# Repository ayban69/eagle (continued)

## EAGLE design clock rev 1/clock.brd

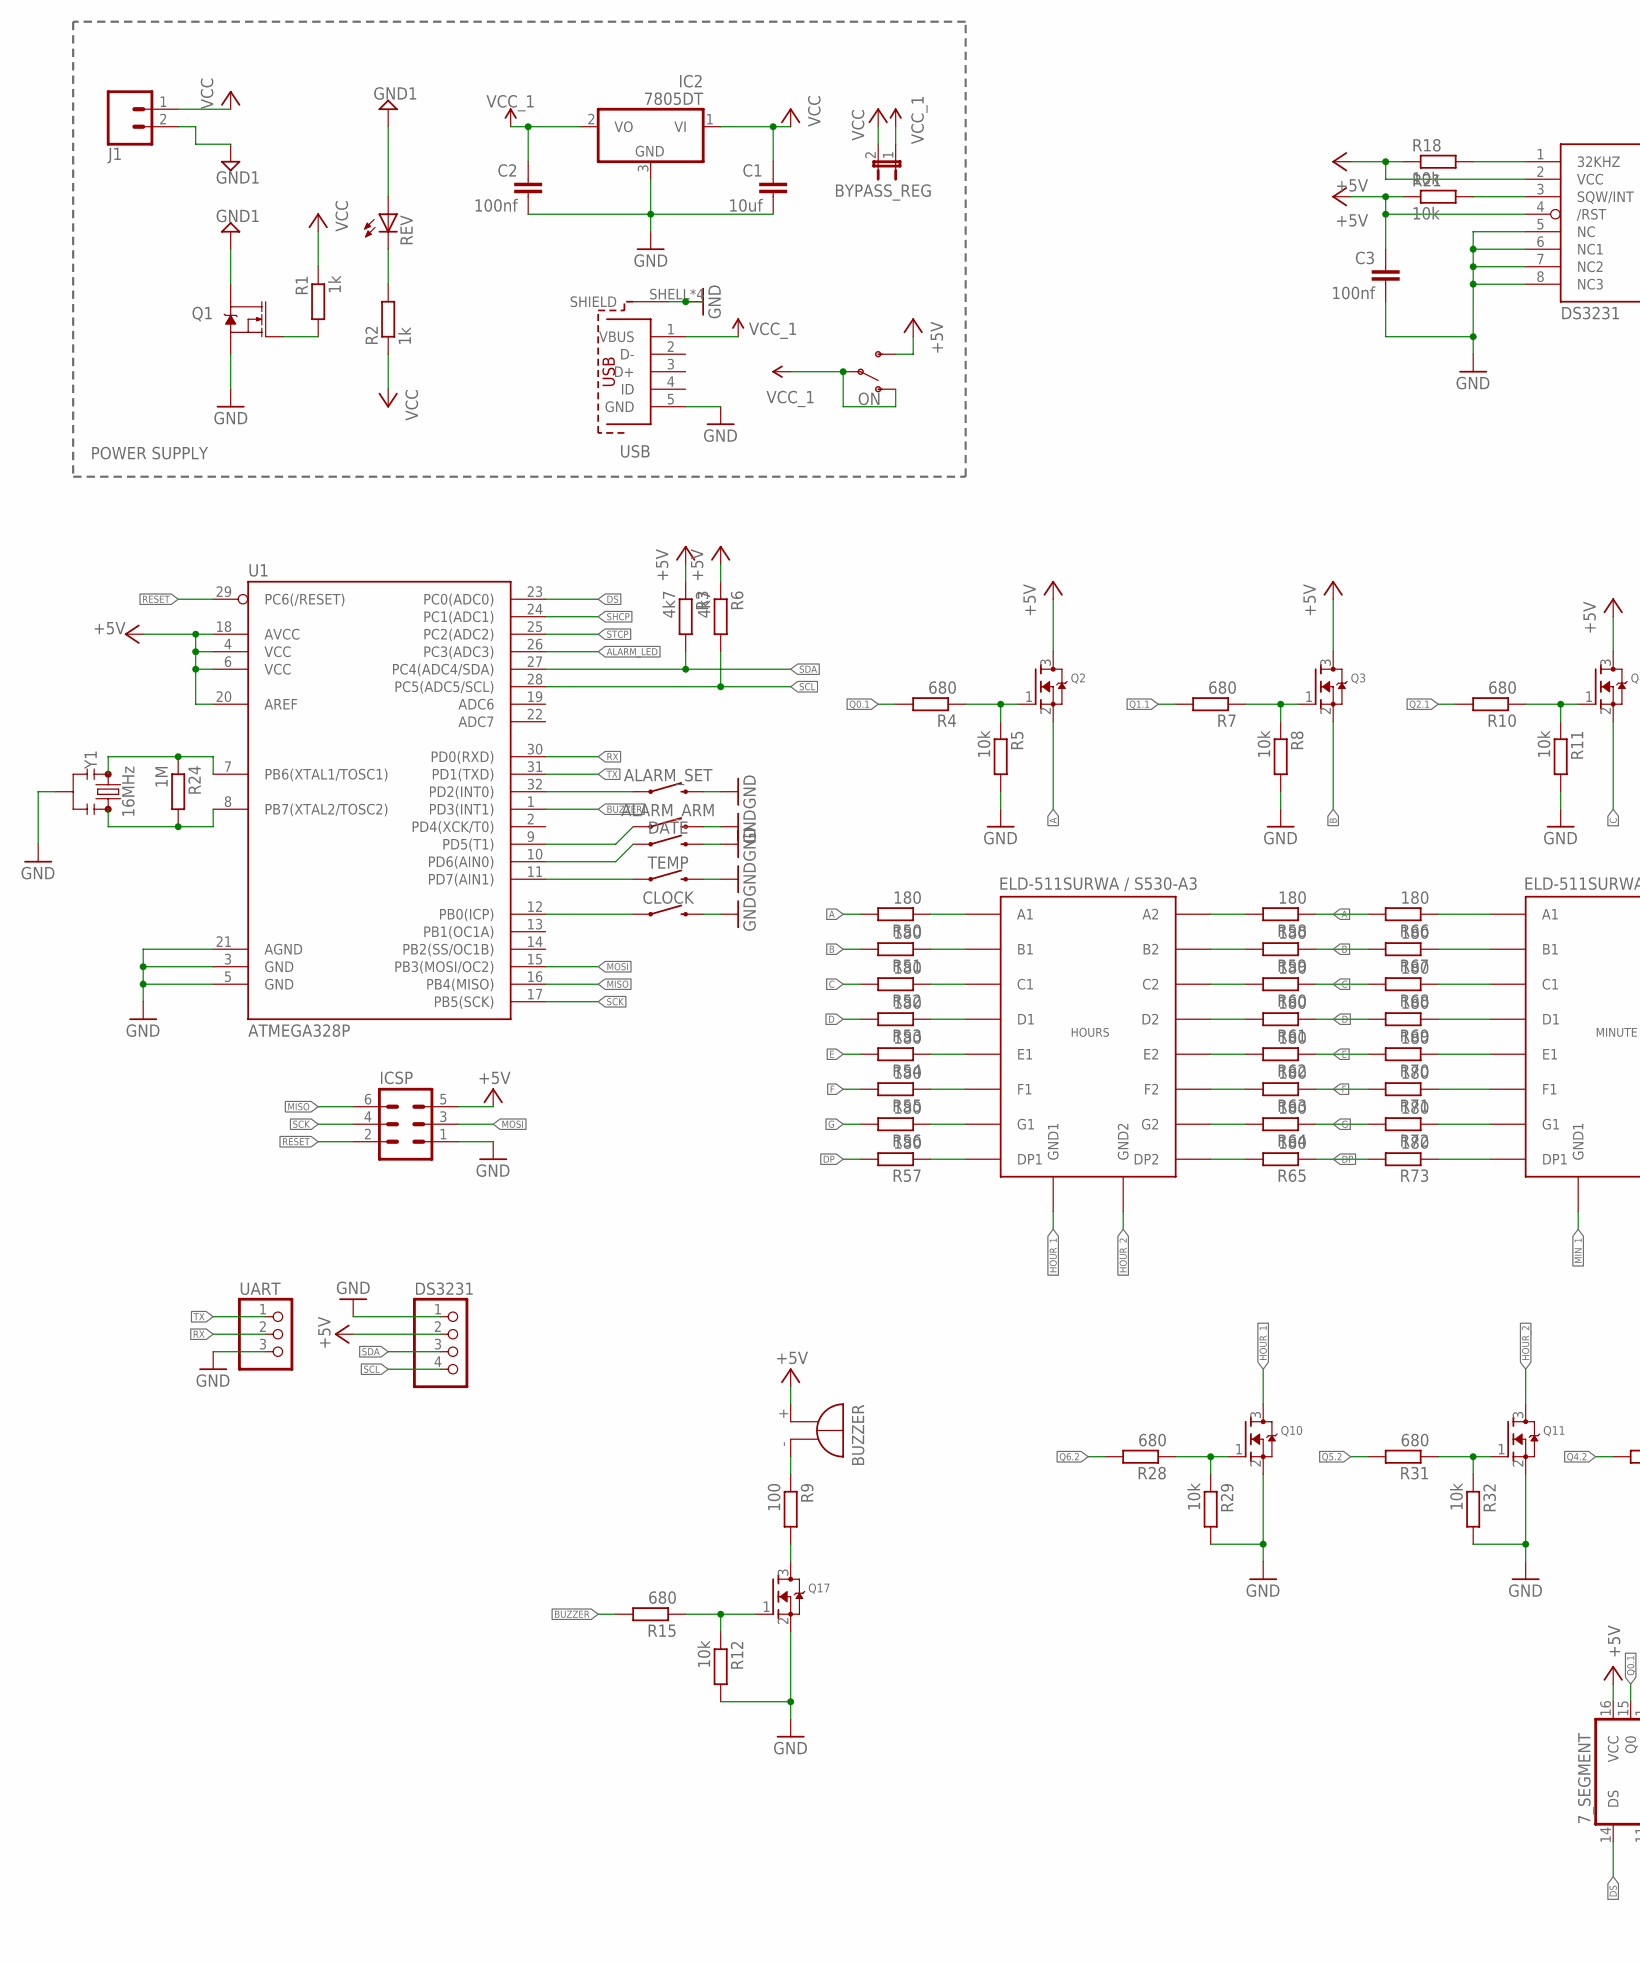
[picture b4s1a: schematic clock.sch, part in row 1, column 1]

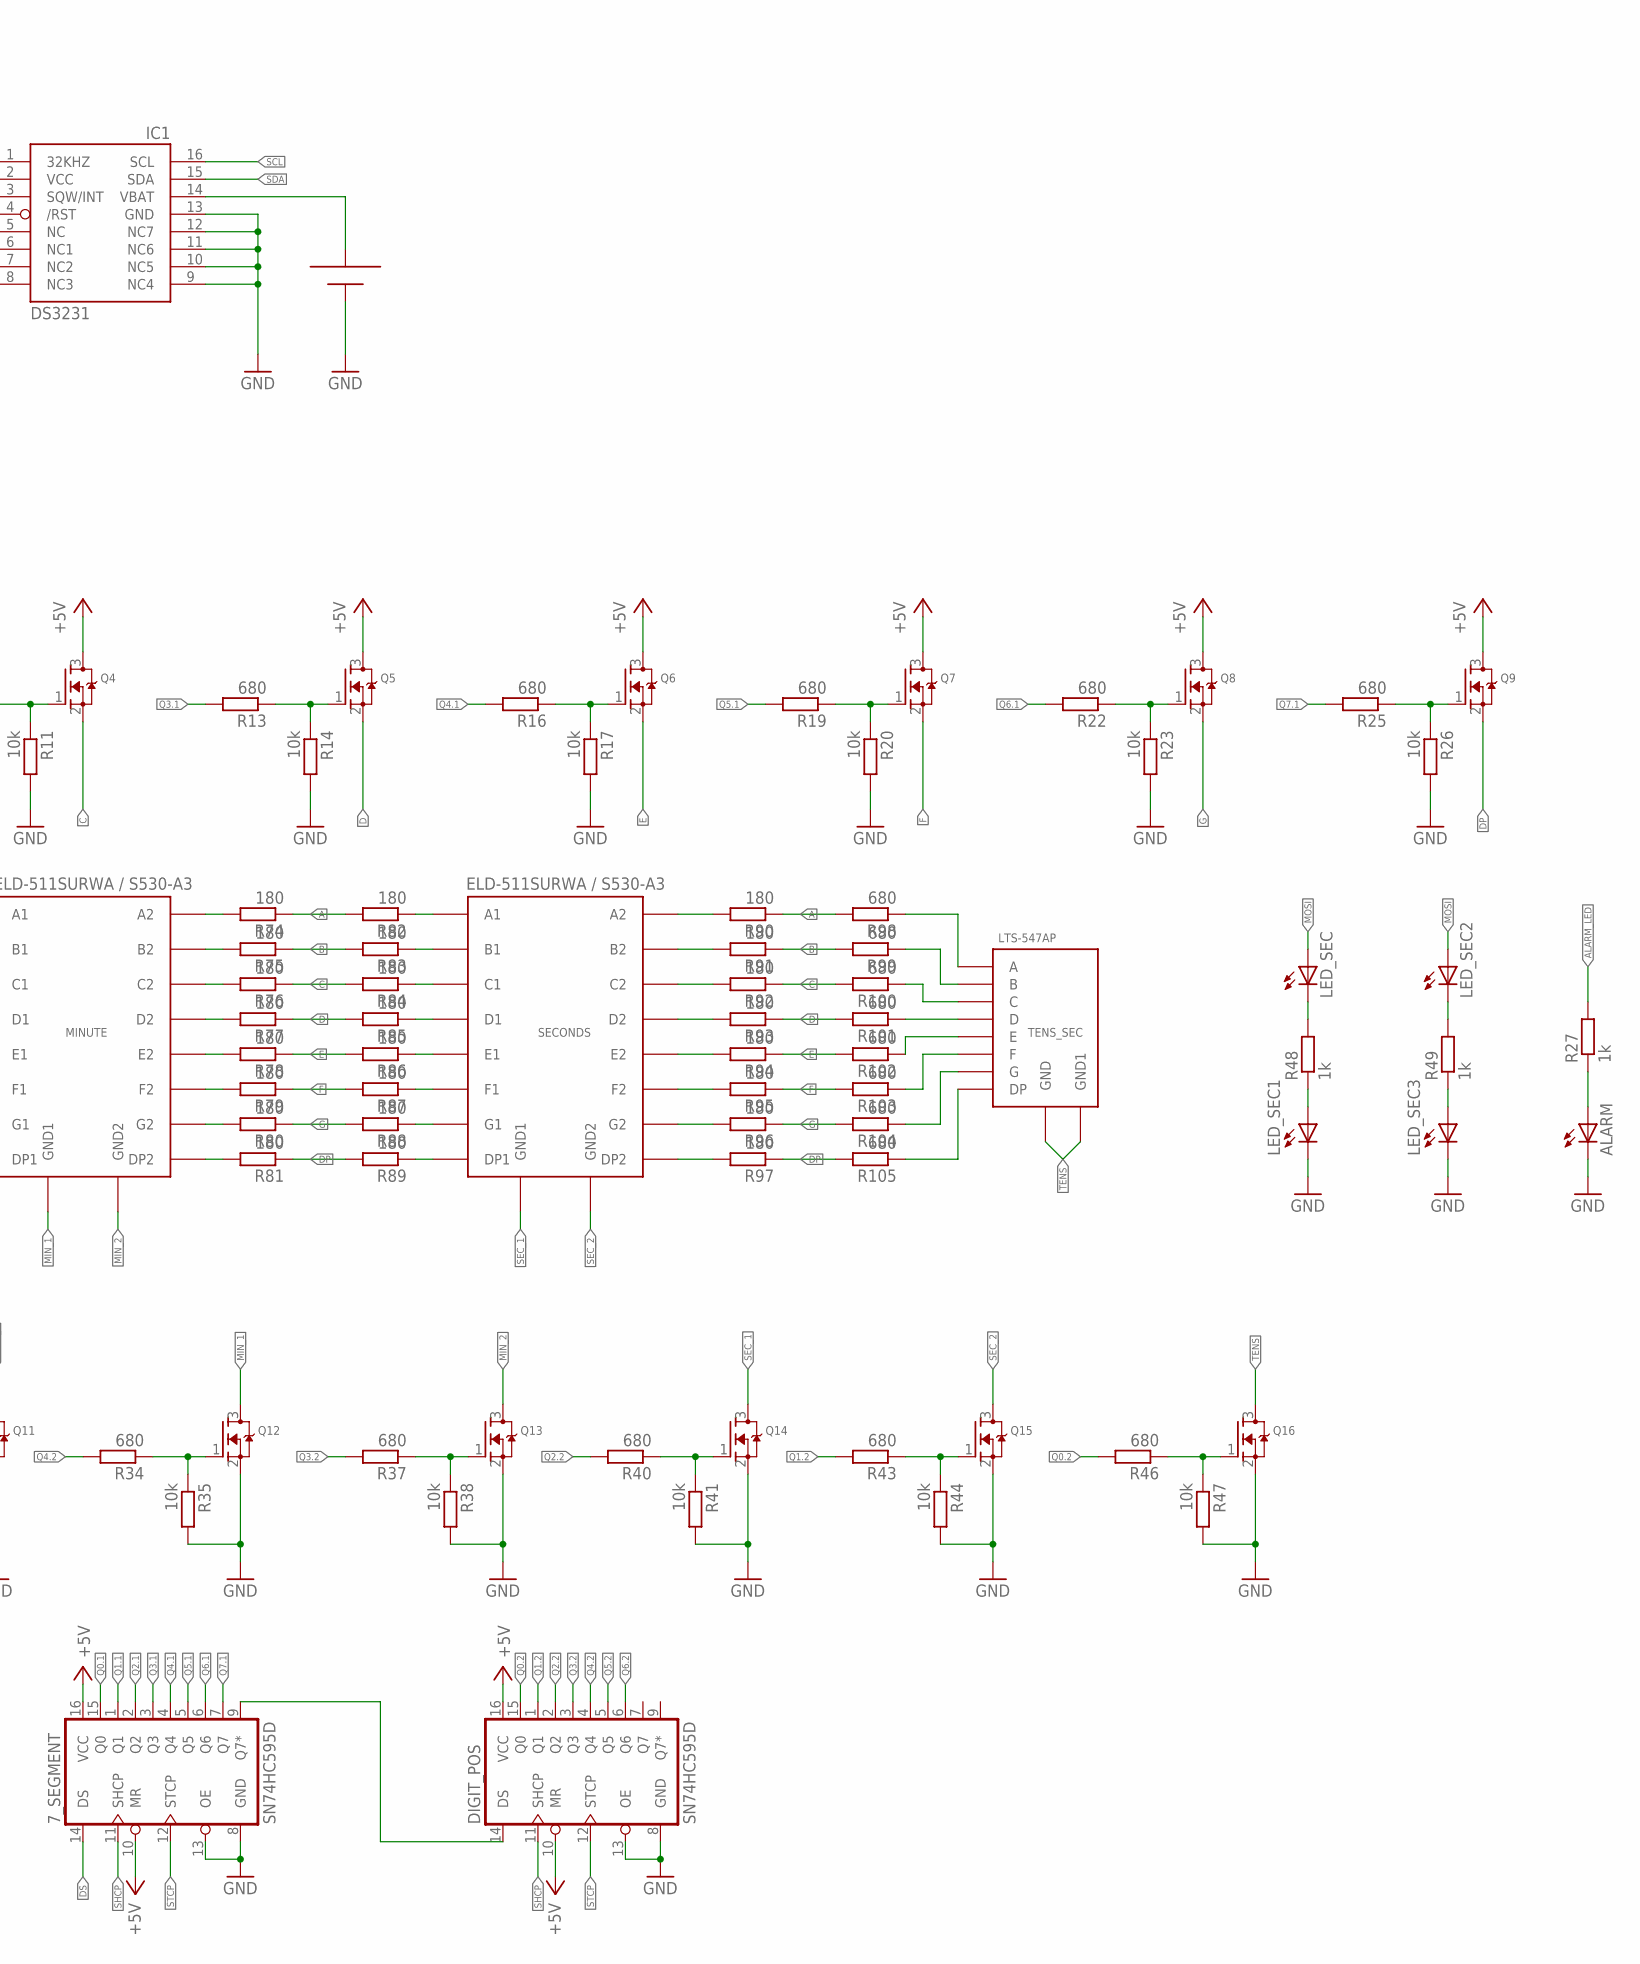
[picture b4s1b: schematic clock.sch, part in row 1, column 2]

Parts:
7_SEGMENT: SN74HC595D; SO16
ALARM: LEDSML0805; SML0805
ALARM_ARM: MOMENTARY-SWITCH-SPST-SMD-5.2MM; TACTILE_SWITCH_SMD_5.2MM
ALARM_SET: MOMENTARY-SWITCH-SPST-SMD-5.2MM; TACTILE_SWITCH_SMD_5.2MM
BUZZER: EB2209A
BYPASS_REG: JUMPER-2PTH; 1X02
C1: 10uf; C1206
C2, C3: 100nf; C1206
CLOCK: MOMENTARY-SWITCH-SPST-SMD-5.2MM; TACTILE_SWITCH_SMD_5.2MM
DATE: MOMENTARY-SWITCH-SPST-SMD-5.2MM; TACTILE_SWITCH_SMD_5.2MM
DIGIT_POS: SN74HC595D; SO16
DS3231: PINHD-1X4; 1X04
HOURS: ELD-511SURWA/S530-A3; 2_DIGITS_7_SEGMENT
IC1: DS3231/SO; SO16W
IC2: 7805DT; TO252
ICSP: MA03-2
J1: CONN_025MM; SCREWTERMINAL-5MM-2
LED_SEC, LED_SEC1, LED_SEC2, LED_SEC3: LEDSML0805; SML0805
MINUTE: ELD-511SURWA/S530-A3; 2_DIGITS_7_SEGMENT
ON: SWITCH-SPDT-PTH-11.6X4.0MM; SWITCH_SPDT_PTH_11.6X4.0MM
Q1: MOSFET-NCH-FDD8780; DPAK
Q2, Q3, Q4, Q5, Q6, Q7, Q8, Q9, Q10, Q11, Q12, Q13, Q14, Q15, Q16, Q17: MOSFET-NREFLOW; SOT23
R1: 1k; R0805
R2, R27, R48, R49: 1k; M0805
R3, R6: 4k7; M0805
R4, R7, R10, R13, R15, R16, R19, R22, R25, R28, R31, R34, R37, R40, R43, R46, R98, R99, R100, R101, R102, R103, R104, R105: 680; M0805
R5, R8, R11, R12, R14, R17, R18, R20, R21, R23, R26, R29, R32, R35, R38, R41, R44, R47: 10k; M0805
R9: 100; M0805
R24: 1M; M0805
R50, R51, R52, R53, R54, R55, R56, R57, R58, R59, R60, R61, R62, R63, R64, R65, R66, R67, R68, R69, R70, R71, R72, R73, R74, R75, R76, R77, R78, R79, R80, R81, R82, R83, R84, R85, R86, R87, R88, R89, R90, R91, R92, R93, R94, R95, R96, R97: 180; M0805
REV: LEDSML0805; SML0805
SECONDS: ELD-511SURWA/S530-A3; 2_DIGITS_7_SEGMENT
TEMP: MOMENTARY-SWITCH-SPST-SMD-5.2MM; TACTILE_SWITCH_SMD_5.2MM
TENS_SEC: LTS-547AP
U1: ATMEGA328P; TQFP32-08
U2: CR2032; SMT_CR2032_HOLDER
UART: PINHD-1X3; 1X03
USB: 629105136821
Y1: 16MHz; RESONATOR-SMD-3.2X1.3

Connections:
+5V: 7_SEGMENT.10 (MR), 7_SEGMENT.16 (VCC), BUZZER.+, C3.1, DIGIT_POS.10 (MR), DIGIT_POS.16 (VCC), DS3231.2, IC1.2 (VCC), IC1.4 (/RST), ICSP.5, ON.3 (S), Q2.3 (D), Q3.3 (D), Q4.3 (D), Q5.3 (D), Q6.3 (D), Q7.3 (D), Q8.3 (D), Q9.3 (D), R3.1, R6.1, R18.1, R21.1, U1.4 (VCC), U1.6 (VCC), U1.18 (AVCC), U1.20 (AREF)
A: Q2.2 (S), R50.2, R58.1, R66.2, R74.1, R82.2, R90.1, R98.2
ALARM_LED: R27.2, U1.26 (PC3(ADC3))
B: Q3.2 (S), R51.2, R59.1, R67.2, R75.1, R83.2, R91.1, R99.2
BUZZER: R15.2, U1.1 (PD3(INT1))
C: Q4.2 (S), R52.2, R60.1, R68.2, R76.1, R84.2, R92.1, R100.2
D: Q5.2 (S), R53.2, R61.1, R69.2, R77.1, R85.2, R93.1, R101.2
DP: Q9.2 (S), R57.2, R65.1, R73.2, R81.1, R89.2, R97.1, R105.2
DS: 7_SEGMENT.14 (DS), U1.23 (PC0(ADC0))
E: Q6.2 (S), R54.2, R62.1, R70.2, R78.1, R86.2, R94.1, R102.2
F: Q7.2 (S), R55.2, R63.1, R71.2, R79.1, R87.2, R95.1, R103.2
G: Q8.2 (S), R56.2, R64.1, R72.2, R80.1, R88.2, R96.1, R104.2
GND: 7_SEGMENT.8 (GND), 7_SEGMENT.13 (OE), ALARM.C, ALARM_ARM.3 (2), ALARM_SET.3 (2), C1.2, C2.2, C3.2, CLOCK.3 (2), DATE.3 (2), DIGIT_POS.8 (GND), DIGIT_POS.13 (OE), DS3231.1, IC1.5 (NC), IC1.6 (NC1), IC1.7 (NC2), IC1.8 (NC3), IC1.9 (NC4), IC1.10 (NC5), IC1.11 (NC6), IC1.12 (NC7), IC1.13 (GND), IC2.3 (GND), ICSP.1, LED_SEC1.C, LED_SEC3.C, Q1.3 (S), Q10.2 (S), Q11.2 (S), Q12.2 (S), Q13.2 (S), Q14.2 (S), Q15.2 (S), Q16.2 (S), Q17.2 (S), R5.2, R8.2, R11.2, R12.2, R14.2, R17.2, R20.2, R23.2, R26.2, R29.2, R32.2, R35.2, R38.2, R41.2, R44.2, R47.2, TEMP.3 (2), U1.3 (GND), U1.5 (GND), U1.21 (AGND), U2.-, UART.3, USB.5 (GND), USB.SHELL (SHIELD), USB.SHELL1 (SHIELD), USB.SHELL2 (SHIELD), USB.SHELL3 (SHIELD), Y1.2
GND1: J1.2, Q1.4 (D), REV.A
HOUR_1: HOURS.GND1, Q10.3 (D)
HOUR_2: HOURS.GND2, Q11.3 (D)
MIN_1: MINUTE.GND1, Q12.3 (D)
MIN_2: MINUTE.GND2, Q13.3 (D)
MISO: ICSP.6, U1.16 (PB4(MISO))
MOSI: ICSP.3, LED_SEC.A, LED_SEC2.A, U1.15 (PB3(MOSI/OC2))
unnamed: Q1.1 (G), R1.2
unnamed: LED_SEC.C, R48.2
unnamed: R24.1, U1.7 (PB6(XTAL1/TOSC1)), Y1.1
unnamed: R24.2, U1.8 (PB7(XTAL2/TOSC2)), Y1.3
unnamed: 7_SEGMENT.9 (Q7*), DIGIT_POS.14 (DS)
unnamed: Q2.1 (G), R4.1, R5.1
unnamed: R2.2, REV.C
unnamed: Q3.1 (G), R7.1, R8.1
unnamed: Q4.1 (G), R10.1, R11.1
unnamed: Q5.1 (G), R13.1, R14.1
unnamed: Q6.1 (G), R16.1, R17.1
unnamed: Q7.1 (G), R19.1, R20.1
unnamed: Q8.1 (G), R22.1, R23.1
unnamed: Q9.1 (G), R25.1, R26.1
unnamed: Q10.1 (G), R28.1, R29.1
unnamed: CLOCK.1, U1.12 (PB0(ICP))
unnamed: TEMP.1, U1.11 (PD7(AIN1))
unnamed: DATE.1, U1.10 (PD6(AIN0))
unnamed: Q11.1 (G), R31.1, R32.1
unnamed: LED_SEC1.A, R48.1
unnamed: LED_SEC2.C, R49.2
unnamed: Q17.1 (G), R12.1, R15.1
unnamed: Q12.1 (G), R34.1, R35.1
unnamed: LED_SEC3.A, R49.1
unnamed: ALARM_SET.1, U1.32 (PD2(INT0))
unnamed: HOURS.A1, R50.1
unnamed: Q13.1 (G), R37.1, R38.1
unnamed: HOURS.B1, R51.1
unnamed: ALARM_ARM.1, U1.9 (PD5(T1))
unnamed: HOURS.C1, R52.1
unnamed: Q14.1 (G), R40.1, R41.1
unnamed: HOURS.D1, R53.1
unnamed: HOURS.E1, R54.1
unnamed: HOURS.F1, R55.1
unnamed: Q15.1 (G), R43.1, R44.1
unnamed: HOURS.G1, R56.1
unnamed: HOURS.DP1, R57.1
unnamed: HOURS.A2, R58.2
unnamed: Q16.1 (G), R46.1, R47.1
unnamed: HOURS.B2, R59.2
unnamed: HOURS.C2, R60.2
unnamed: HOURS.D2, R61.2
unnamed: HOURS.E2, R62.2
unnamed: HOURS.F2, R63.2
unnamed: HOURS.G2, R64.2
unnamed: HOURS.DP2, R65.2
unnamed: MINUTE.A2, R74.2
unnamed: MINUTE.A1, R66.1
unnamed: MINUTE.B1, R67.1
unnamed: MINUTE.C1, R68.1
unnamed: MINUTE.B2, R75.2
unnamed: MINUTE.C2, R76.2
unnamed: MINUTE.D2, R77.2
unnamed: MINUTE.E2, R78.2
unnamed: MINUTE.F2, R79.2
unnamed: MINUTE.G2, R80.2
unnamed: MINUTE.DP2, R81.2
unnamed: MINUTE.DP1, R73.1
unnamed: MINUTE.G1, R72.1
unnamed: MINUTE.F1, R71.1
unnamed: MINUTE.E1, R70.1
unnamed: MINUTE.D1, R69.1
unnamed: Q17.3 (D), R9.2
unnamed: BUZZER.-, R9.1
unnamed: R89.1, SECONDS.DP1
unnamed: R88.1, SECONDS.G1
unnamed: R87.1, SECONDS.F1
unnamed: R86.1, SECONDS.E1
unnamed: IC1.14 (VBAT), U2.+
unnamed: IC1.3 (SQW/INT), R21.2
unnamed: IC1.1 (32KHZ), R18.2
unnamed: ALARM.A, R27.1
unnamed: R82.1, SECONDS.A1
unnamed: R83.1, SECONDS.B1
unnamed: R84.1, SECONDS.C1
unnamed: R85.1, SECONDS.D1
unnamed: R90.2, SECONDS.A2
unnamed: R91.2, SECONDS.B2
unnamed: R92.2, SECONDS.C2
unnamed: R93.2, SECONDS.D2
unnamed: R94.2, SECONDS.E2
unnamed: R95.2, SECONDS.F2
unnamed: R96.2, SECONDS.G2
unnamed: R97.2, SECONDS.DP2
unnamed: R98.1, TENS_SEC.A
unnamed: R99.1, TENS_SEC.B
unnamed: R100.1, TENS_SEC.C
unnamed: R101.1, TENS_SEC.D
unnamed: R102.1, TENS_SEC.E
unnamed: R103.1, TENS_SEC.F
unnamed: R104.1, TENS_SEC.G
unnamed: R105.1, TENS_SEC.DP
Q0.1: 7_SEGMENT.15 (Q0), R4.2
Q0.2: DIGIT_POS.15 (Q0), R46.2
Q1.1: 7_SEGMENT.1 (Q1), R7.2
Q1.2: DIGIT_POS.1 (Q1), R43.2
Q2.1: 7_SEGMENT.2 (Q2), R10.2
Q2.2: DIGIT_POS.2 (Q2), R40.2
Q3.1: 7_SEGMENT.3 (Q3), R13.2
Q3.2: DIGIT_POS.3 (Q3), R37.2
Q4.1: 7_SEGMENT.4 (Q4), R16.2
Q4.2: DIGIT_POS.4 (Q4), R34.2
Q5.1: 7_SEGMENT.5 (Q5), R19.2
Q5.2: DIGIT_POS.5 (Q5), R31.2
Q6.1: 7_SEGMENT.6 (Q6), R22.2
Q6.2: DIGIT_POS.6 (Q6), R28.2
Q7.1: 7_SEGMENT.7 (Q7), R25.2
RESET: ICSP.2, U1.29 (PC6(/RESET))
RX: U1.30 (PD0(RXD)), UART.2
SCK: ICSP.4, U1.17 (PB5(SCK))
SCL: DS3231.4, IC1.16 (SCL), R6.2, U1.28 (PC5(ADC5/SCL))
SDA: DS3231.3, IC1.15 (SDA), R3.2, U1.27 (PC4(ADC4/SDA))
SEC_1: Q14.3 (D), SECONDS.GND1
SEC_2: Q15.3 (D), SECONDS.GND2
SHCP: 7_SEGMENT.11 (SHCP), DIGIT_POS.11 (SHCP), U1.24 (PC1(ADC1))
STCP: 7_SEGMENT.12 (STCP), DIGIT_POS.12 (STCP), U1.25 (PC2(ADC2))
TENS: Q16.3 (D), TENS_SEC.GND, TENS_SEC.GND1
TX: U1.31 (PD1(TXD)), UART.1
VCC: BYPASS_REG.2, C1.1, IC2.1 (VI), J1.1, R1.1, R2.1
VCC_1: BYPASS_REG.1, C2.1, IC2.2 (VO), ON.1 (O), ON.2, USB.1 (VBUS)

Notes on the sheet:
POWER SUPPLY

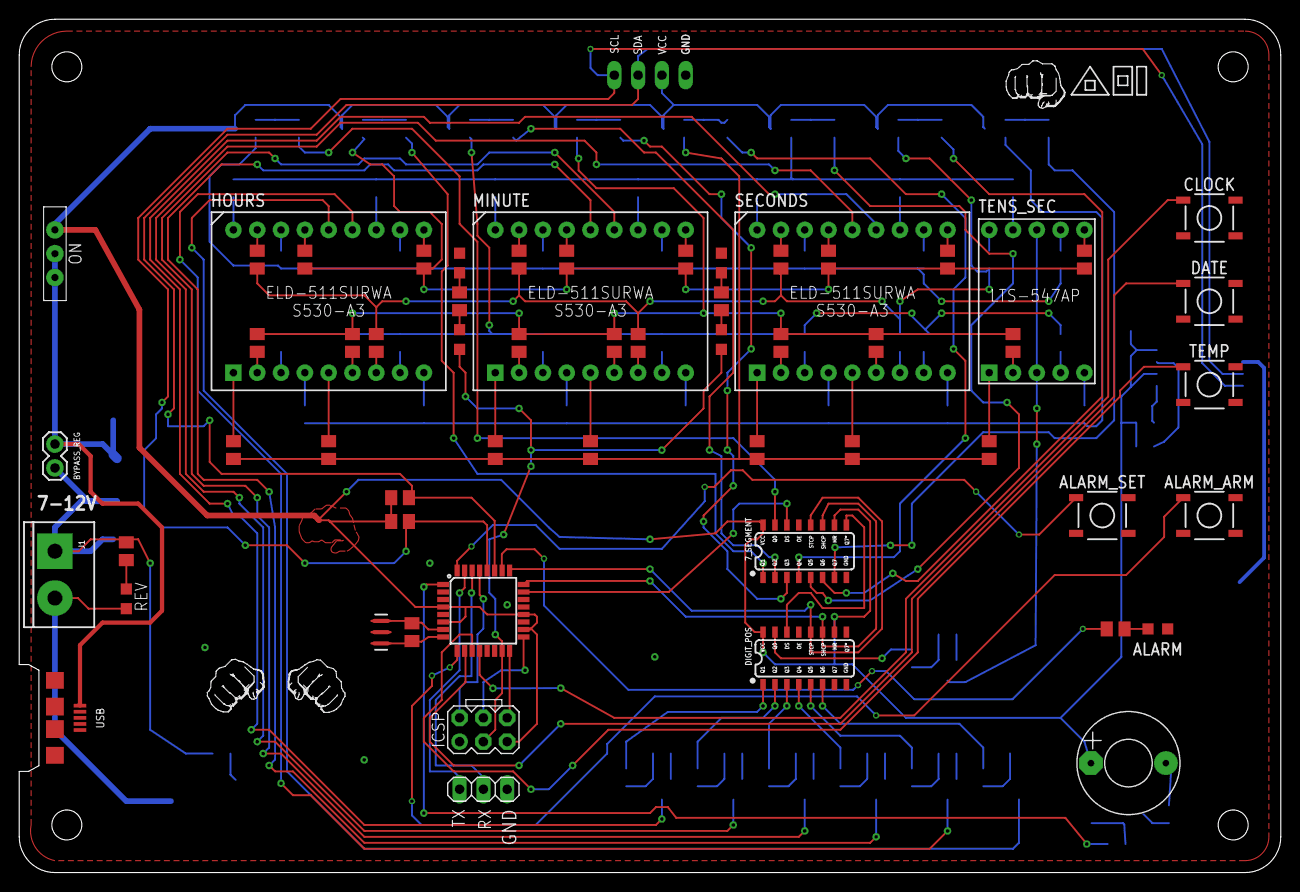
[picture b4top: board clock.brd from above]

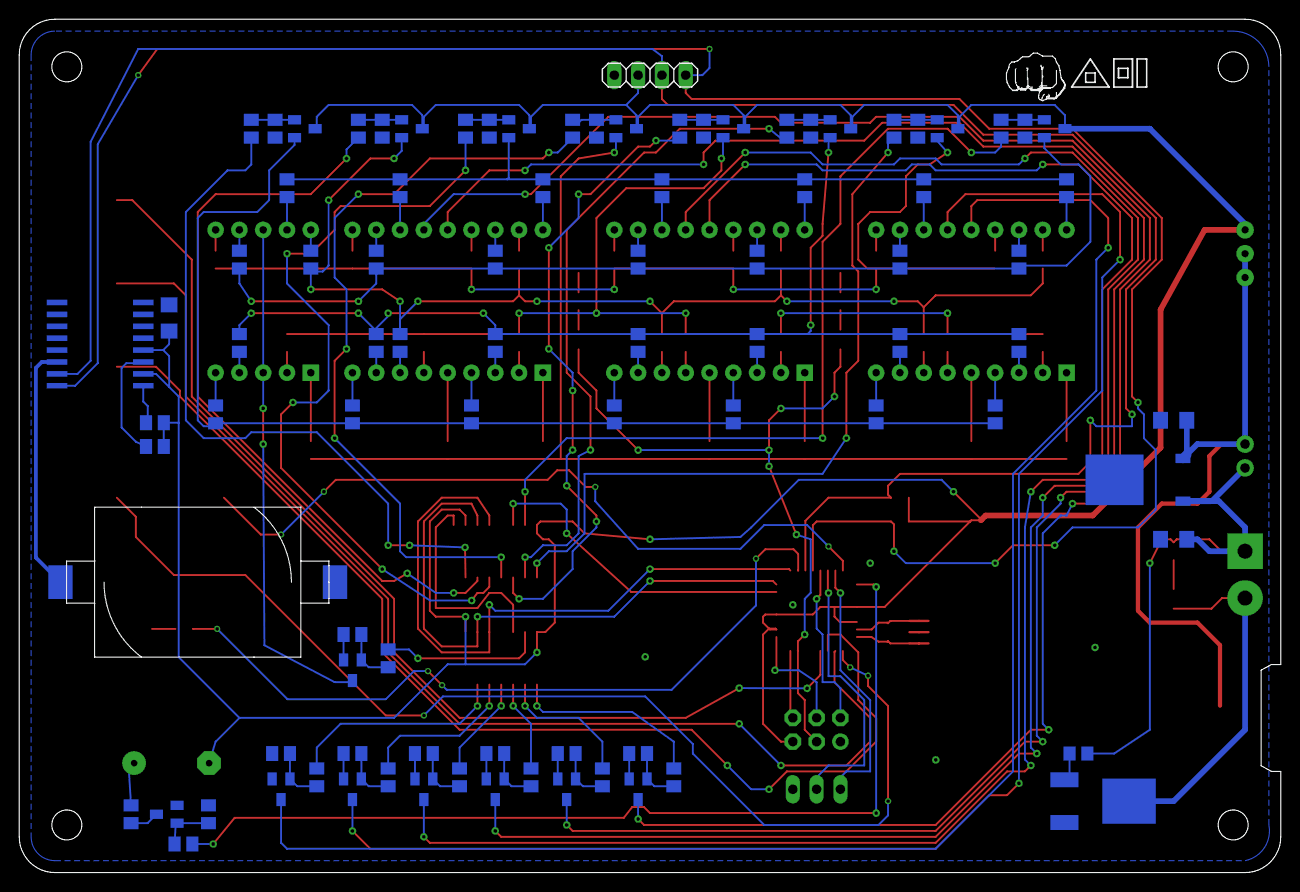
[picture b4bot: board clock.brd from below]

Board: 2 copper layers, 134.6 x 91.1 mm, 152 parts (91 on the bottom side), 140 nets.

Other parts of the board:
U$1, U$2, U$4: ADILOGO

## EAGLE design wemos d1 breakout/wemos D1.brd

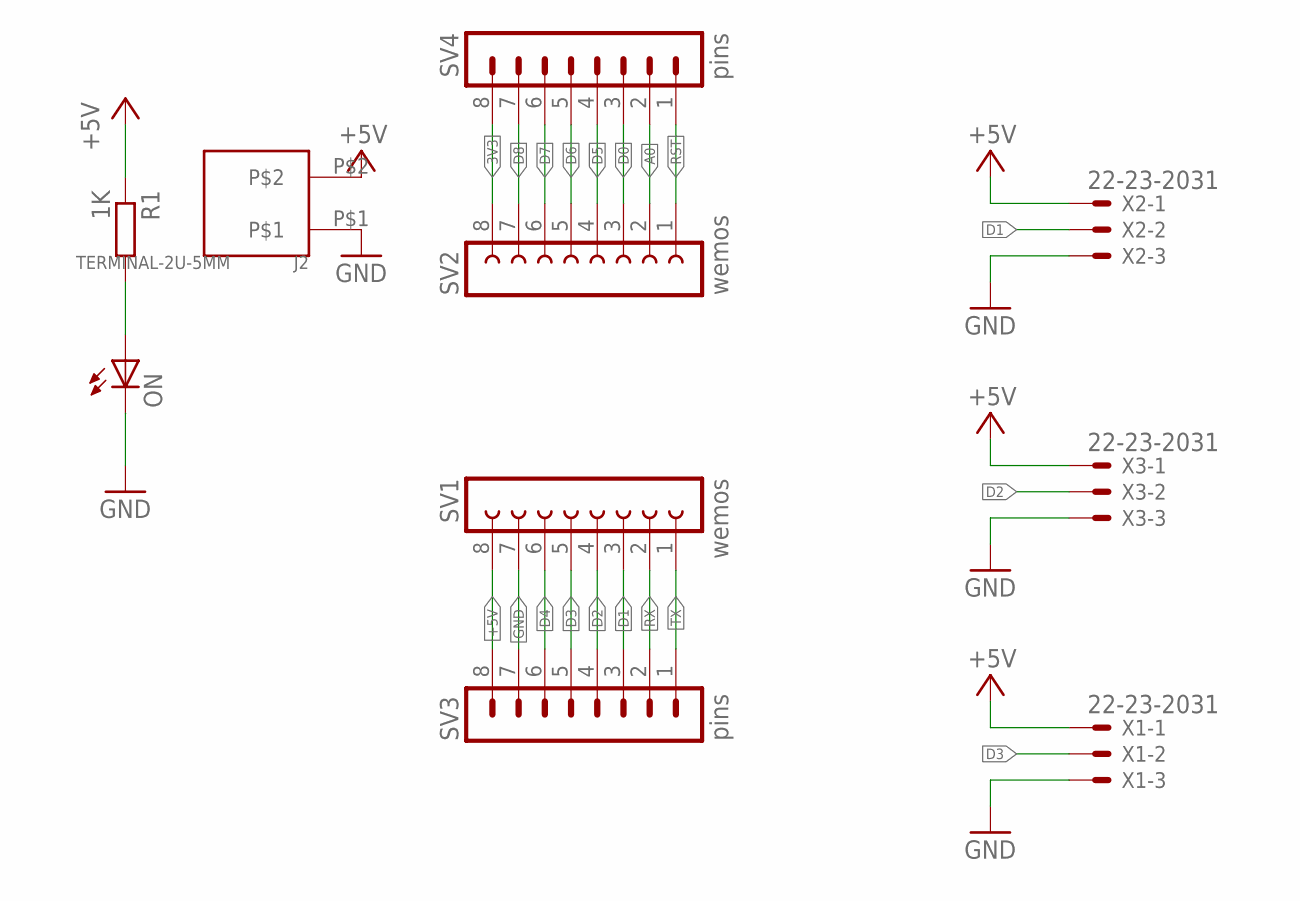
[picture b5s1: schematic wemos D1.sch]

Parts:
1K: R1; R0805
J2: TERMINAL-2U-5MM
ON: SML0805
SV1, SV2: wemos; FE08
SV3, SV4: pins; MA08-1
X1, X2, X3: 22-23-2031

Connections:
3V3: SV2.8, SV4.8
+5V: 1K.1, J2.P$2, SV1.8, SV3.8, X1.1, X2.1, X3.1
A0: SV2.2, SV4.2
D0: SV2.3, SV4.3
D1: SV1.3, SV3.3, X2.2
D2: SV1.4, SV3.4, X3.2
D3: SV1.5, SV3.5, X1.2
D4: SV1.6, SV3.6
D5: SV2.4, SV4.4
D6: SV2.5, SV4.5
D7: SV2.6, SV4.6
D8: SV2.7, SV4.7
GND: J2.P$1, ON.C, SV1.7, SV3.7, X1.3, X2.3, X3.3
unnamed: 1K.2, ON.A
RST: SV2.1, SV4.1
RX: SV1.2, SV3.2
TX: SV1.1, SV3.1

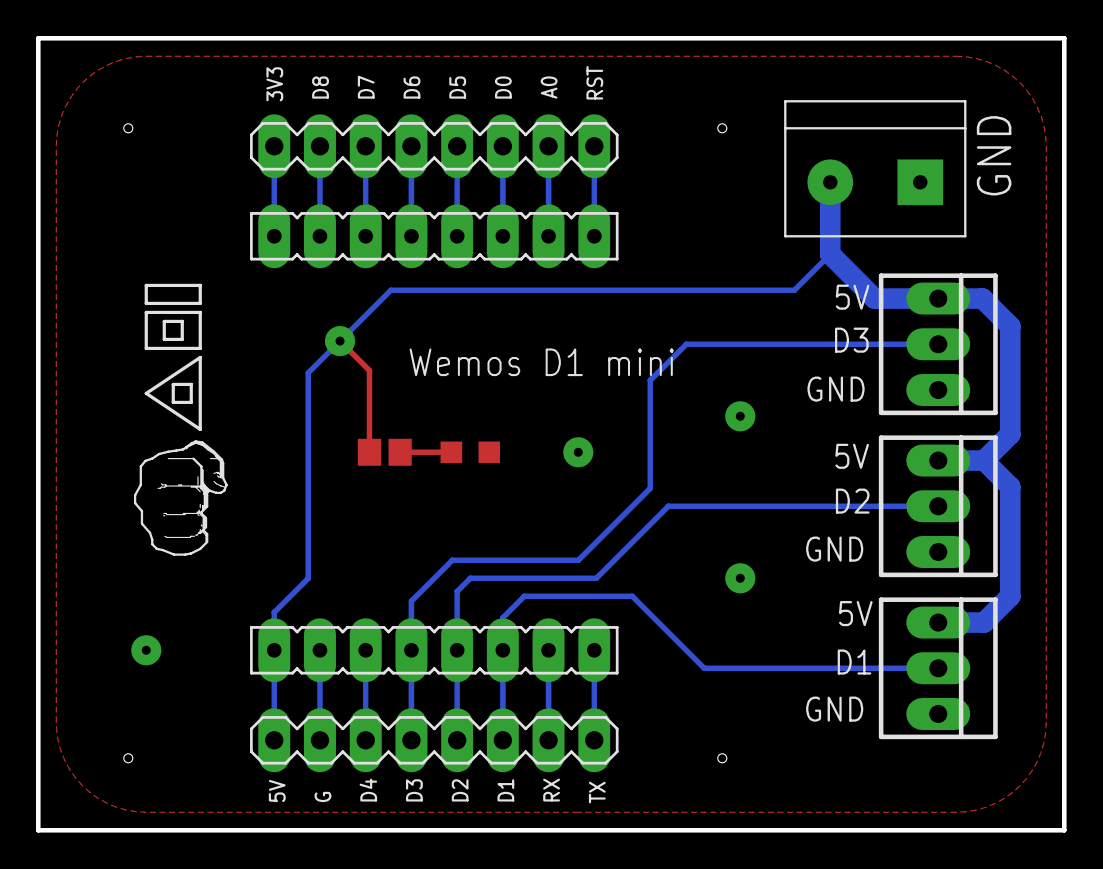
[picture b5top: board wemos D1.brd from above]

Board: 2 copper layers, 57.0 x 44.0 mm, 11 parts (0 on the bottom side), 17 nets.

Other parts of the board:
U$1: ADILOGO

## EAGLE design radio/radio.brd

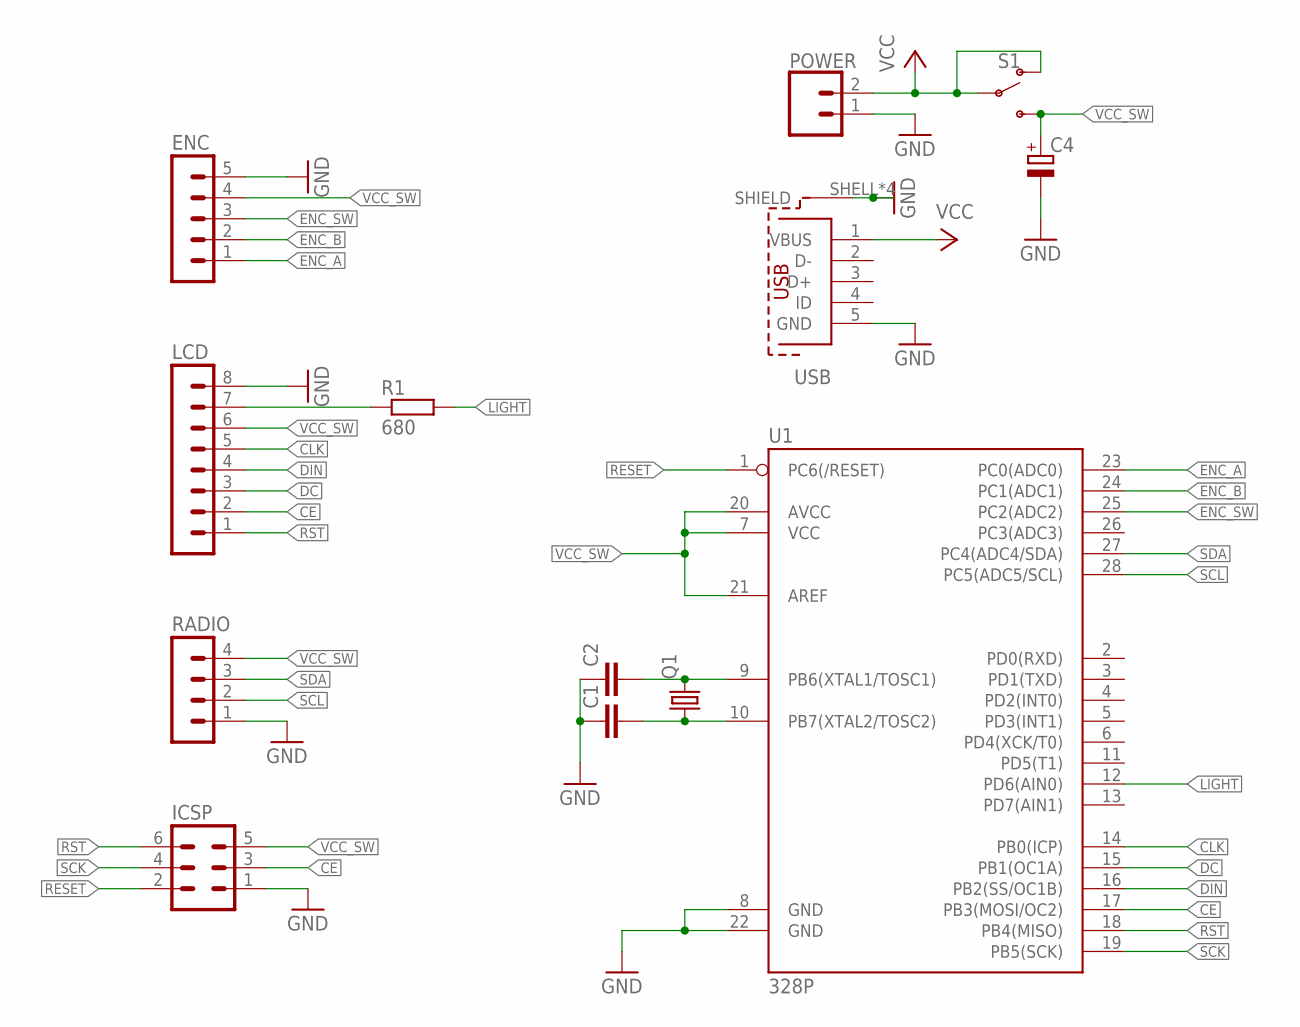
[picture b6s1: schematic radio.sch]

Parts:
C1, C2: C-EUC1206; C1206
C4: CPOL-EUE5-10.5; E5-10,5
ENC: MA05-1
ICSP: MA03-2
LCD: MA08-1
POWER: CONN_02PTH3; 1X02_LONGPADS
Q1: CRYSTALSM49; SM49
R1: 680; R0805
RADIO: MA04-1
S1: SWITCH-SPDT-PTH-11.6X4.0MM; SWITCH_SPDT_PTH_11.6X4.0MM
U1: 328P; DIP28
USB: 629105136821

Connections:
CE: ICSP.3, LCD.2, U1.17 (PB3(MOSI/OC2))
CLK: LCD.5, U1.14 (PB0(ICP))
DC: LCD.3, U1.15 (PB1(OC1A))
DIN: LCD.4, U1.16 (PB2(SS/OC1B))
ENC_A: ENC.1, U1.23 (PC0(ADC0))
ENC_B: ENC.2, U1.24 (PC1(ADC1))
ENC_SW: ENC.3, U1.25 (PC2(ADC2))
GND: C1.1, C2.1, C4.-, ENC.5, ICSP.1, LCD.8, POWER.1, RADIO.1, U1.8 (GND), U1.22 (GND), USB.5 (GND), USB.SHELL (SHIELD), USB.SHELL1 (SHIELD), USB.SHELL2 (SHIELD), USB.SHELL3 (SHIELD)
LIGHT: R1.2, U1.12 (PD6(AIN0))
unnamed: C2.2, Q1.2, U1.9 (PB6(XTAL1/TOSC1))
unnamed: C1.2, Q1.1, U1.10 (PB7(XTAL2/TOSC2))
unnamed: LCD.7, R1.1
RESET: ICSP.2, U1.1 (PC6(/RESET))
RST: ICSP.6, LCD.1, U1.18 (PB4(MISO))
SCK: ICSP.4, U1.19 (PB5(SCK))
SCL: RADIO.2, U1.28 (PC5(ADC5/SCL))
SDA: RADIO.3, U1.27 (PC4(ADC4/SDA))
VCC: POWER.2, S1.1 (O), S1.2, USB.1 (VBUS)
VCC_SW: C4.+, ENC.4, ICSP.5, LCD.6, RADIO.4, S1.3 (S), U1.7 (VCC), U1.20 (AVCC), U1.21 (AREF)

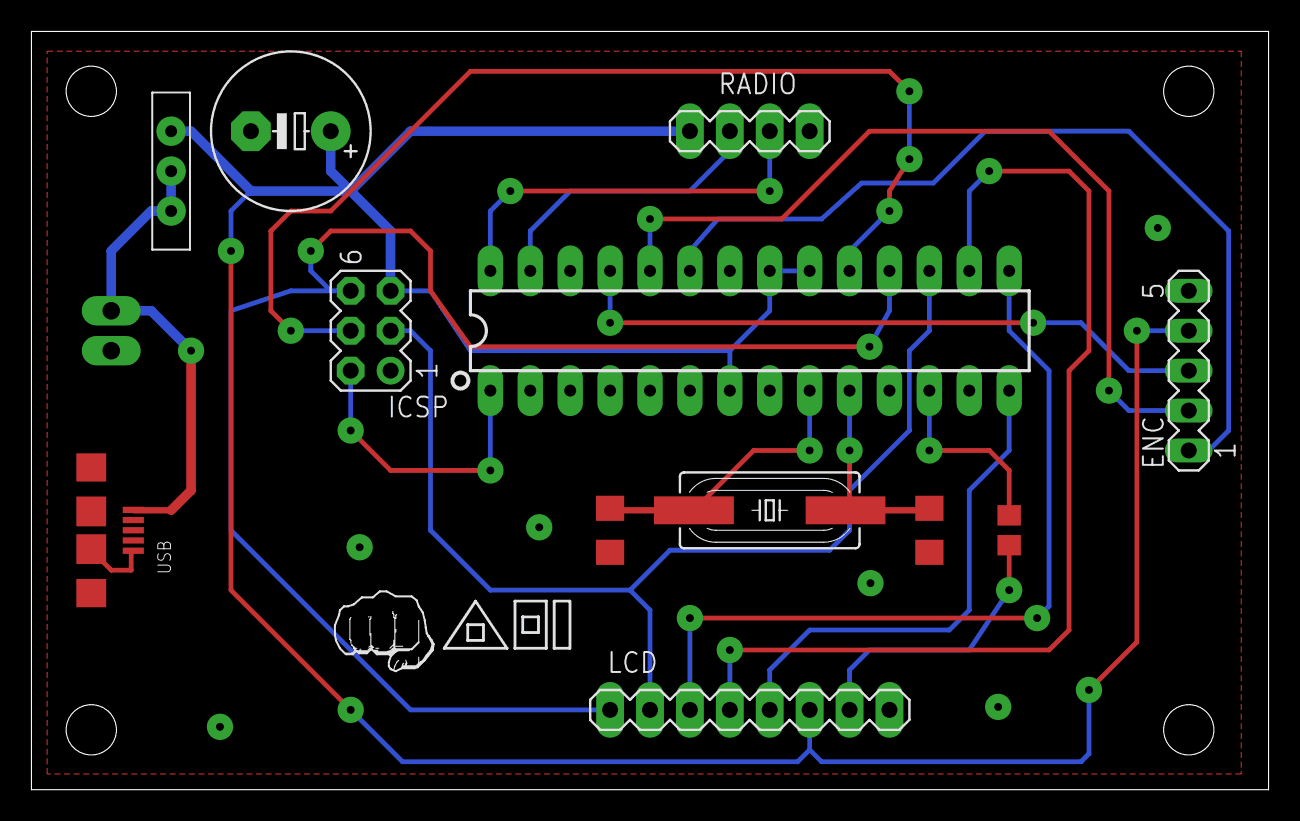
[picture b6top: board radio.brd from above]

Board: 2 copper layers, 78.7 x 48.3 mm, 14 parts (0 on the bottom side), 19 nets.

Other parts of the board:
U$1: ADILOGO

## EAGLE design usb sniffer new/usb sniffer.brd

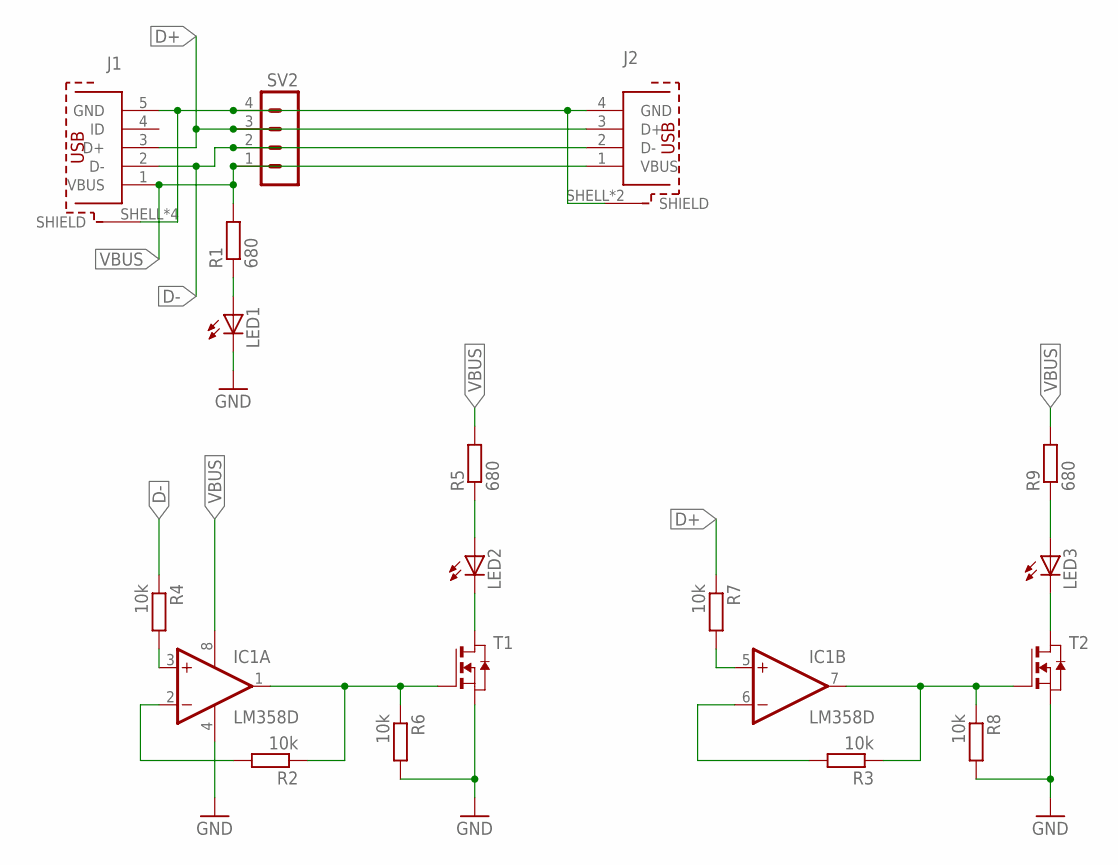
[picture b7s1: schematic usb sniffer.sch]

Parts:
IC1: LM358D; SO08
J1: 629105136821
J2: 61400416021
LED1, LED2, LED3: LEDSML0805; SML0805
R1, R5, R9: 680; R0805
R2, R3, R4, R6, R7, R8: 10k; R0805
SV2: MA04-1
T1, T2: NMOSSOT23; SOT-23

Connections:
D+: J1.3 (D+), J2.3 (D+), R7.1, SV2.3
D-: J1.2 (D-), J2.2 (D-), R4.1, SV2.2
GND: IC1.4 (V-), J1.5 (GND), J1.SHELL (SHIELD), J1.SHELL1 (SHIELD), J1.SHELL2 (SHIELD), J1.SHELL3 (SHIELD), J2.4 (GND), J2.SHELL (SHIELD), J2.SHELL1 (SHIELD), LED1.C, R6.2, R8.2, SV2.4, T1.2 (S), T2.2 (S)
unnamed: LED1.A, R1.1
unnamed: LED2.C, T1.1 (D)
unnamed: IC1.2 (-IN), R2.2
unnamed: IC1.1 (OUT), R2.1, R6.1, T1.3 (G)
unnamed: LED2.A, R5.1
unnamed: IC1.6 (-IN), R3.2
unnamed: IC1.7 (OUT), R3.1, R8.1, T2.3 (G)
unnamed: IC1.3 (+IN), R4.2
unnamed: IC1.5 (+IN), R7.2
unnamed: LED3.C, T2.1 (D)
unnamed: LED3.A, R9.1
VBUS: IC1.8 (V+), J1.1 (VBUS), J2.1 (VBUS), R1.2, R5.2, R9.2, SV2.1

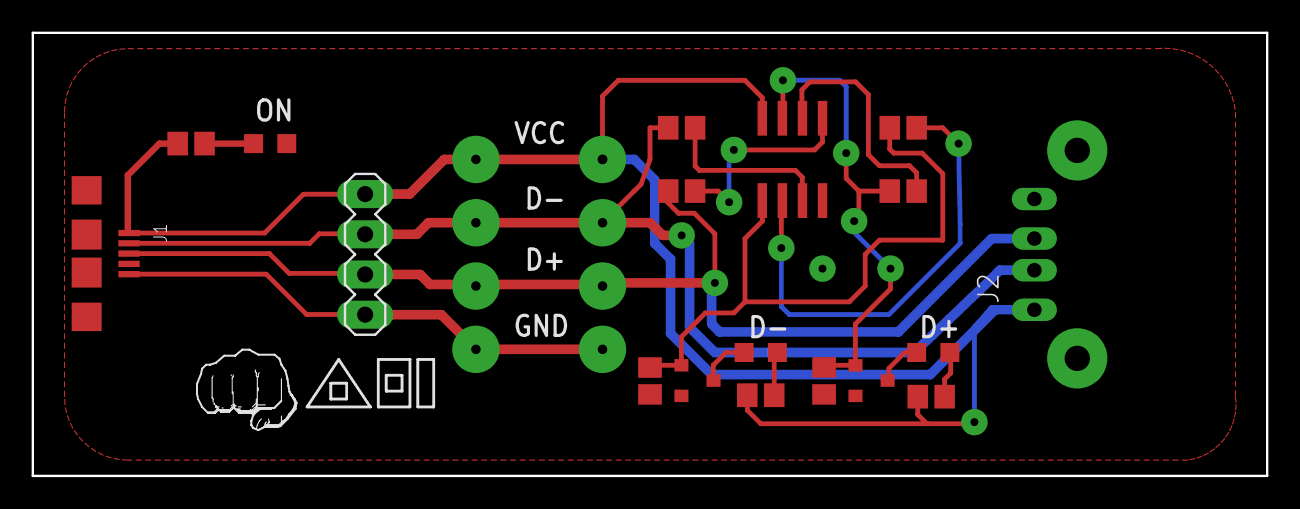
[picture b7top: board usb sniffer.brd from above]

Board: 2 copper layers, 78.0 x 28.0 mm, 19 parts (0 on the bottom side), 15 nets.

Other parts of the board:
U$1: ADILOGO

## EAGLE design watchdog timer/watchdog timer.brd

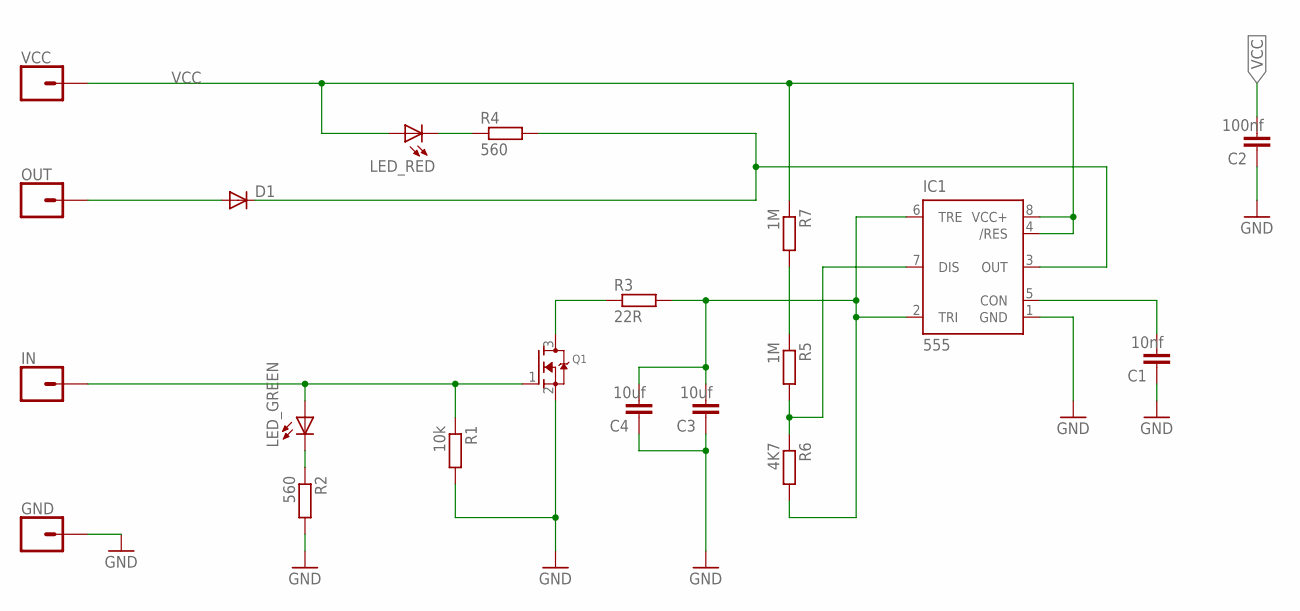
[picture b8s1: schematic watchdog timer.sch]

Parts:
C1: 10nf; C1206
C2: 100nf; C1206
C3, C4: 10uf; C1206
D1: DIODE-SOD323-W; SOD323-W
GND: CONN_01; 1X01
IC1: 555; SO08
IN: CONN_01; 1X01
LED_GREEN: LEDSML0805; SML0805
LED_RED: LEDSML0805; SML0805
OUT: CONN_01; 1X01
Q1: MOSFET-NREFLOW; SOT23
R1: 10k; M0805
R2, R4: 560; M0805
R3: 22R; M0805
R5, R7: 1M; M0805
R6: 4K7; M0805
VCC: CONN_01; 1X01

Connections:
GND: C1.1, C2.1, C3.1, C4.1, GND.1, IC1.1 (GND), Q1.2 (S), R1.2, R2.2
IN: IN.1, LED_GREEN.A, Q1.1 (G), R1.1
unnamed: IC1.7 (DIS), R5.2, R6.1
unnamed: LED_GREEN.C, R2.1
unnamed: R5.1, R7.2
unnamed: D1.A, OUT.1
unnamed: C1.2, IC1.5 (CON)
unnamed: D1.C, IC1.3 (OUT), R4.2
unnamed: Q1.3 (D), R3.1
unnamed: C3.2, C4.2, IC1.2 (TRI), IC1.6 (TRE), R3.2, R6.2
unnamed: LED_RED.C, R4.1
VCC: C2.2, IC1.4 (/RES), IC1.8 (VCC+), LED_RED.A, R7.1, VCC.1
